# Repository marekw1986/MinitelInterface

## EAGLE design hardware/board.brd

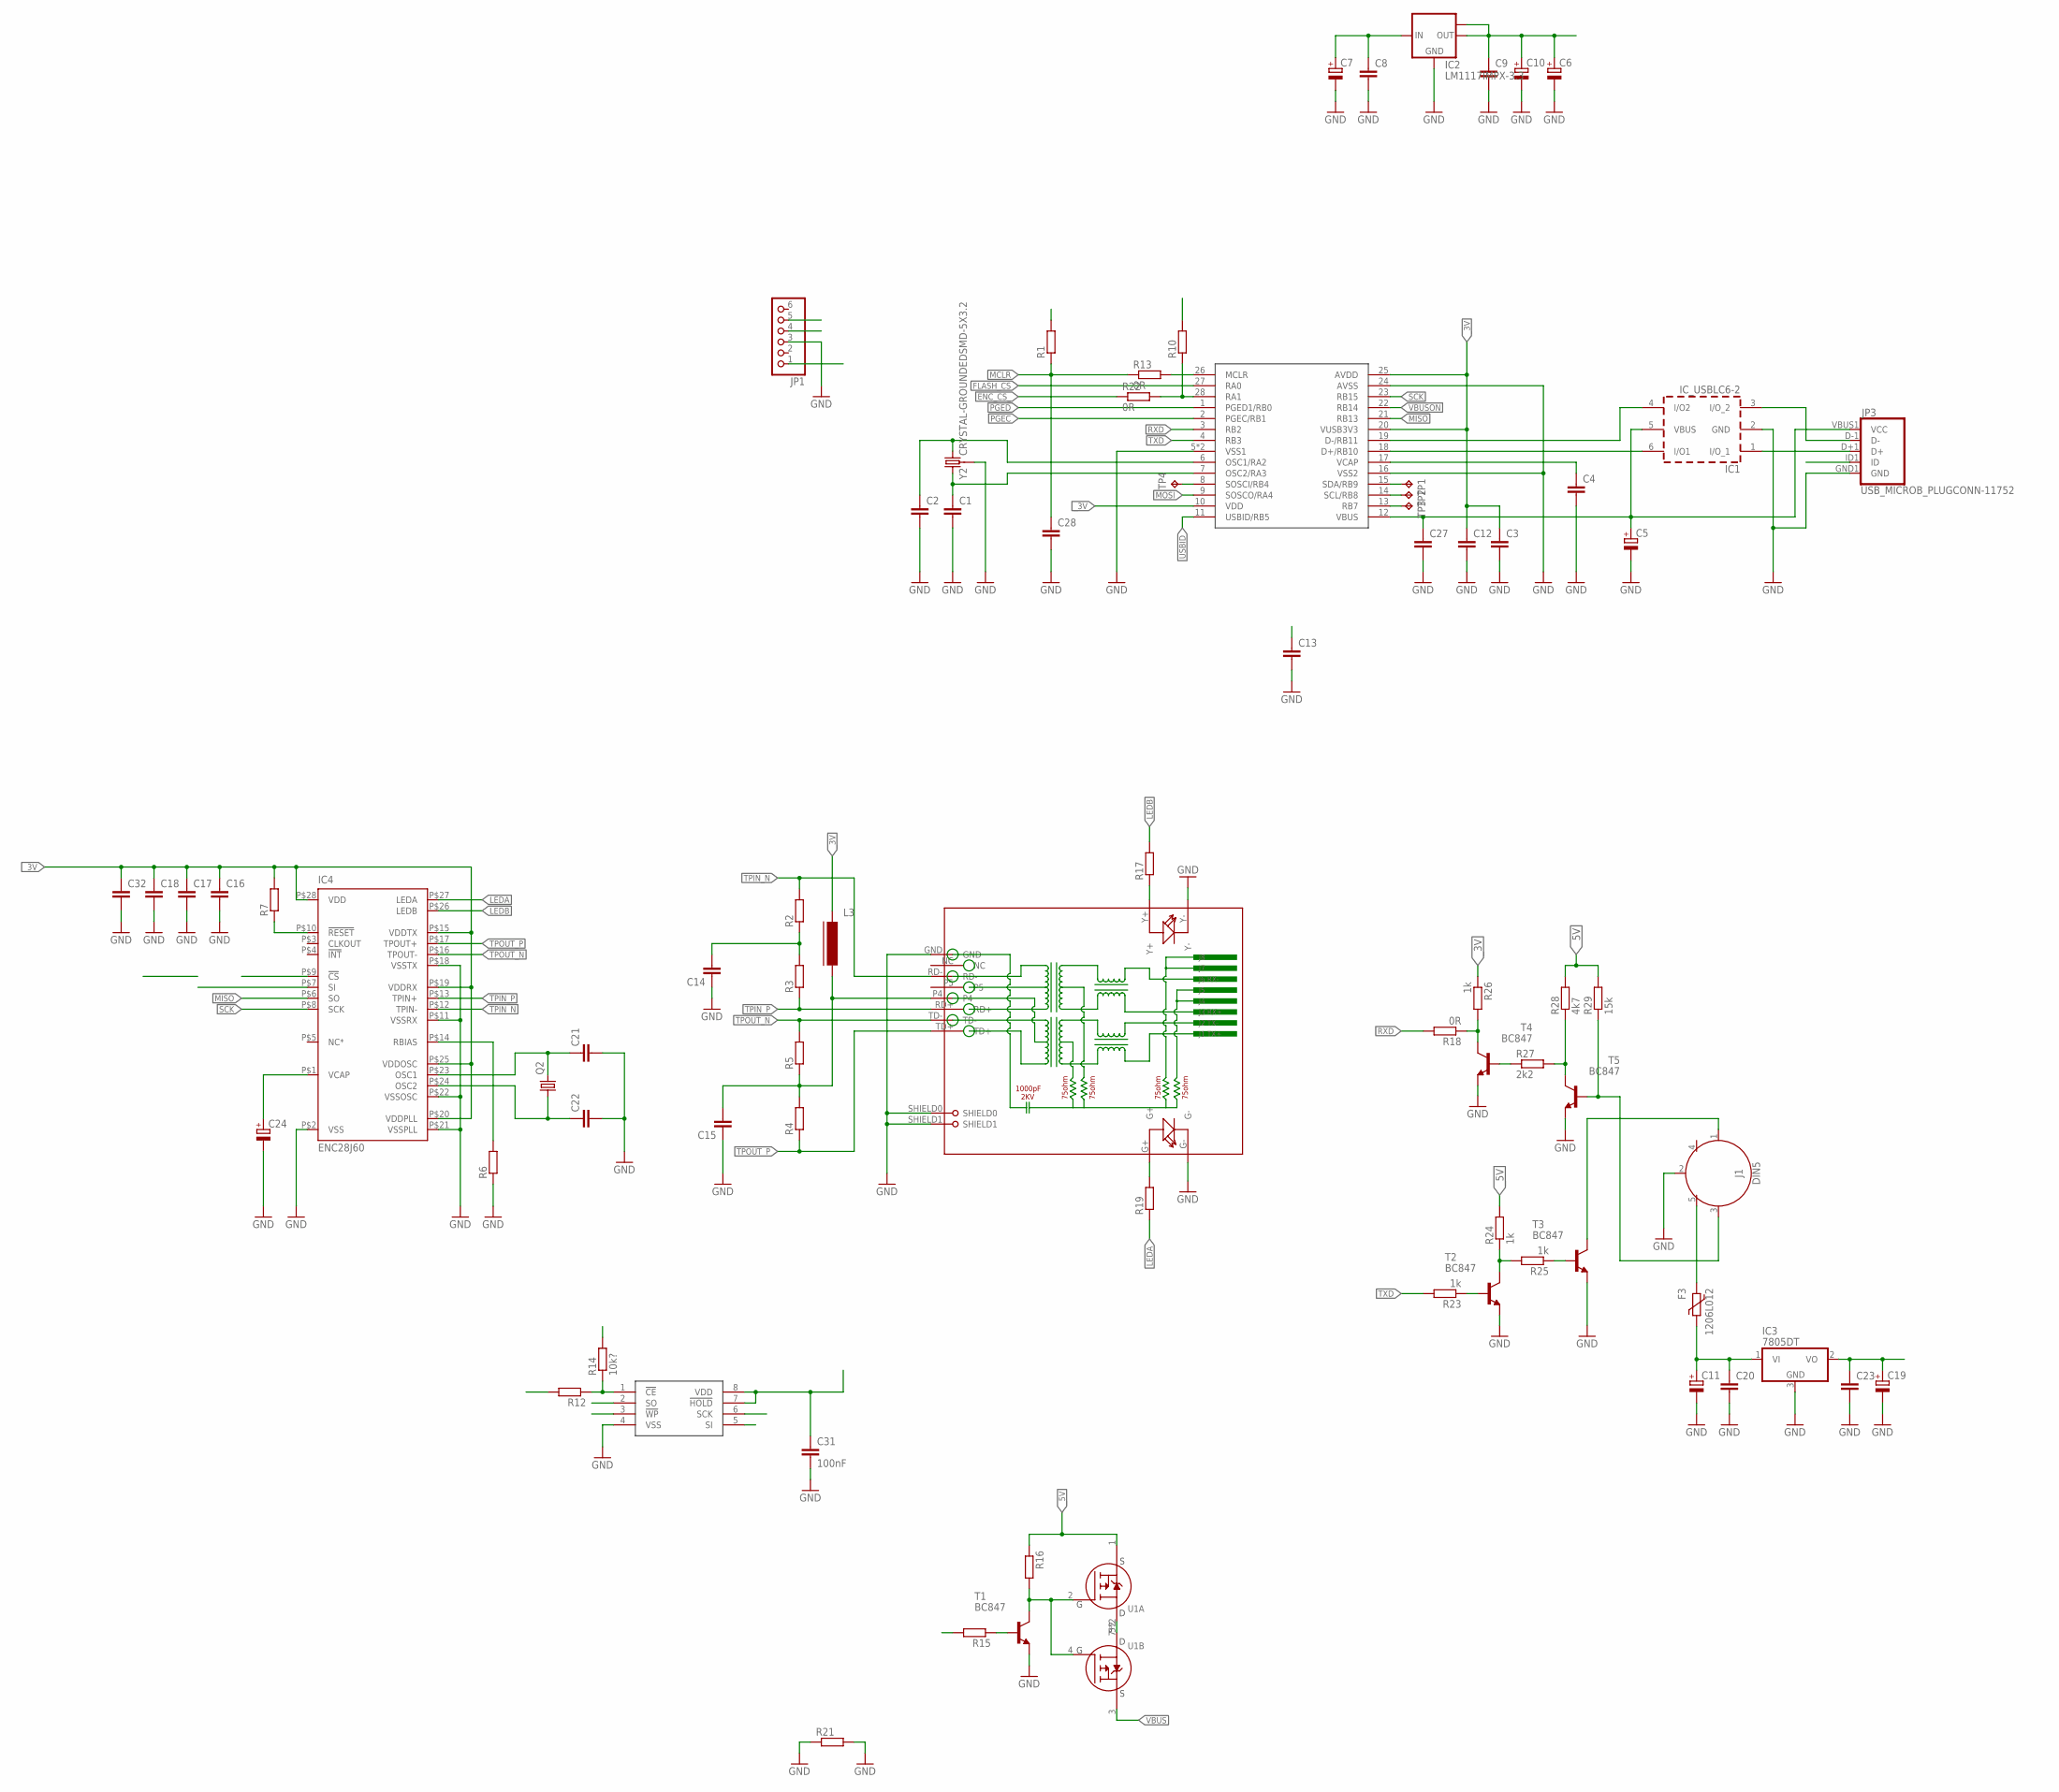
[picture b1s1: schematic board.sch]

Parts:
C1, C2, C4, C8, C9, C12, C13, C14, C15, C20, C21, C22, C23, C27, C28: C-EUC0603; C0603
C3, C16, C17, C18, C32: C-EUC0402; C0402
C5, C6, C24: CPOL-EUSMCA; SMC_A
C7, C11, C19: CPOL-EUSMCC; SMC_C
C10: CPOL-EUSMCB; SMC_B
C31: 100nF; C0603
F3: 1206L012; 1206L
IC1: IC_USBLC6-2; SOT-23-6L
IC2: LM1117IMPX-3.3; SOT223
IC3: 7805DT; TO252
IC4: ENC28J60; TSSOP28W
J1: DIN5; DIN5-RA-PTH
JP1: PINHD-1X6; 1X06
JP3: USB_MICROB_PLUGCONN-11752; USB-B-MICRO-SMD_V03
L3: FERRITE-0805; FB805
Q2: CRYSTALHC49S; HC49/S
R1, R2, R3, R4, R5, R7, R10, R12, R15: R-EU_R0603; R0603
R6: R-EU_R0805; R0805
R13, R22: 0R; R0603
R14: 10k?; R0603
R16: R-EU_R0402; R0402
R17, R19, R21: R-EU_R1206; R1206
R18: 0R; R1206
R23: 1k; R1206
R24, R25, R26: 1k; R0603
R27: 2k2; R0603
R28: 4k7; R0603
R29: 15k; R0603
RJ1: HR911105A
T1, T2, T3, T4, T5: BC847; SOT23
TP1, TP2, TP3, TP4: TPTP16R; TP16R
U1: IRF7314_P_MOSFET; SO-8
U$1: PIC32MX250F128B; QFN-S28-6X6
U$2: SST25VF016BSO8M; SO-08M
Y2: CRYSTAL-GROUNDEDSMD-5X3.2; CRYSTAL-SMD-5X3.2-4PAD

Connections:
D_N: IC1.4 (I/O2), U$1.19 (D-/RB11)
D_P: IC1.6 (I/O1), U$1.18 (D+/RB10)
ENC_CS_: IC4.P$9 (!CS), R22.1
ENC_RST: IC4.P$10 (!RESET), R7.1
FLASH_CS: R12.2, U$1.27 (RA0)
GND: C1.2, C2.2, C3.2, C4.2, C5.-, C6.-, C7.-, C8.2, C9.2, C10.-, C11.-, C12.2, C13.2, C14.1, C15.1, C16.2, C17.2, C18.2, C19.-, C20.2, C21.2, C22.2, C23.2, C24.-, C27.2, C28.2, C31.2, C32.2, IC1.2 (GND), IC2.1 (GND), IC3.3 (GND), IC4.P$2 (VSS), IC4.P$11 (VSSRX), IC4.P$18 (VSSTX), IC4.P$21 (VSSPLL), IC4.P$22 (VSSOSC), J1.2, JP1.3, JP3.GND1 (GND), R6.1, R21.1, R21.2, RJ1.G-, RJ1.GND, RJ1.SHIELD0, RJ1.SHIELD1, RJ1.Y-, T1.2 (E), T2.2 (E), T3.2 (E), T4.2 (E), T5.2 (E), U$1.5 (VSS1), U$1.16 (VSS2), U$1.24 (AVSS), U$1.EXP (VSS1), U$2.4 (VSS), Y2.2 (3), Y2.4 (3)
IO_INT: TP3.TP, U$1.13 (RB7)
LEDA: IC4.P$27 (LEDA), R19.1
LEDB: IC4.P$26 (LEDB), R17.2
MCLR: C28.1, JP1.1, R1.1, R13.1
MCLR_: R13.2, U$1.26 (MCLR)
MISO: IC4.P$6 (SO), U$1.21 (RB13), U$2.2 (SO)
MOSI: IC4.P$7 (SI), U$1.9 (SOSCO/RA4), U$2.5 (SI)
unnamed: R15.1, T1.1 (B)
unnamed: C14.2, R2.1, R3.2
unnamed: J1.1, T3.3 (C)
unnamed: C1.1, U$1.7 (OSC2/RA3), Y2.3 (1)
unnamed: C2.1, U$1.6 (OSC1/RA2), Y2.1 (2)
unnamed: C15.2, L3.2, R4.2, R5.1, RJ1.P4
unnamed: C4.1, U$1.17 (VCAP)
unnamed: F3.2, J1.5
unnamed: IC1.1 (I/O_1), JP3.D+1 (D+)
unnamed: IC1.3 (I/O_2), JP3.D-1 (D-)
unnamed: R12.1, R14.1, U$2.1 (!CE)
unnamed: IC4.P$14 (RBIAS), R6.2
unnamed: R16.2, T1.3 (C), U1.2 (G), U1.4 (G)
unnamed: R10.1, R22.2, U$1.28 (RA1)
unnamed: U1.5 (D), U1.6 (D), U1.7 (D), U1.8 (D)
unnamed: R23.1, T2.1 (B)
unnamed: C21.1, IC4.P$23 (OSC1), Q2.2
unnamed: C22.1, IC4.P$24 (OSC2), Q2.1
unnamed: R24.1, R25.2, T2.3 (C)
unnamed: R25.1, T3.1 (B)
unnamed: R27.1, T4.1 (B)
unnamed: R18.1, R26.2, T4.3 (C)
unnamed: R27.2, R28.1, T5.3 (C)
unnamed: C24.+, IC4.P$1 (VCAP)
unnamed: R17.1, RJ1.Y+
unnamed: R19.2, RJ1.G+
unnamed: J1.3, R29.1, T5.1 (B)
unnamed: C11.+, C20.1, F3.1, IC3.1 (VI)
PGEC: JP1.5, U$1.2 (PGEC/RB1)
PGED: JP1.4, U$1.1 (PGED1/RB0)
RX: TP2.TP, U$1.14 (SCL/RB8)
RXD: R18.2, U$1.3 (RB2)
SCK: IC4.P$8 (SCK), U$1.23 (RB15), U$2.6 (SCK)
SIG: TP4.TP, U$1.8 (SOSCI/RB4)
TPIN_N: IC4.P$12 (TPIN-), R2.2, RJ1.RD-
TPIN_P: IC4.P$13 (TPIN+), R3.1, RJ1.RD+
TPOUT_N: IC4.P$16 (TPOUT-), R5.2, RJ1.TD-
TPOUT_P: IC4.P$17 (TPOUT+), R4.1, RJ1.TD+
TX: TP1.TP, U$1.15 (SDA/RB9)
TXD: R23.2, U$1.4 (RB3)
USBID: JP3.ID1 (ID), U$1.11 (USBID/RB5)
VBUS: C5.+, C27.1, IC1.5 (VBUS), JP3.VBUS1 (VCC), U1.3 (S), U$1.12 (VBUS)
VBUSON: R15.2, U$1.22 (RB14)
_3V: C3.1, C6.+, C9.1, C10.+, C12.1, C13.1, C16.1, C17.1, C18.1, C31.1, C32.1, IC2.2 (OUT), IC2.TAB (OUT1), IC4.P$15 (VDDTX), IC4.P$19 (VDDRX), IC4.P$20 (VDDPLL), IC4.P$25 (VDDOSC), IC4.P$28 (VDD), L3.1, R1.2, R7.2, R10.2, R14.2, R26.1, U$1.10 (VDD), U$1.20 (VUSB3V3), U$1.25 (AVDD), U$2.3 (!WP), U$2.7 (!HOLD), U$2.8 (VDD)
_5V: C7.+, C8.1, C19.+, C23.1, IC2.3 (IN), IC3.2 (VO), R16.1, R24.2, R28.2, R29.2, U1.1 (S)

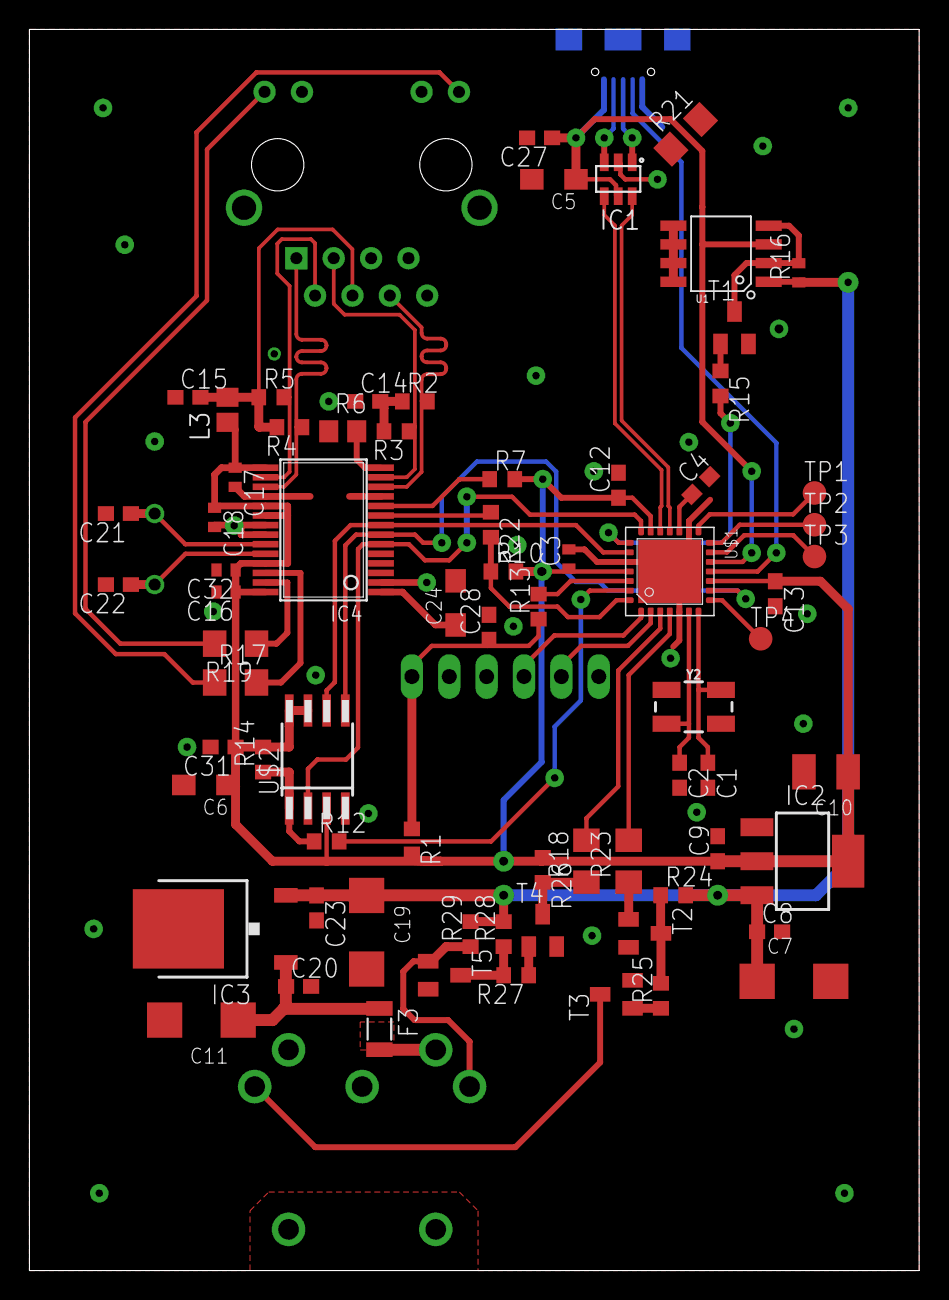
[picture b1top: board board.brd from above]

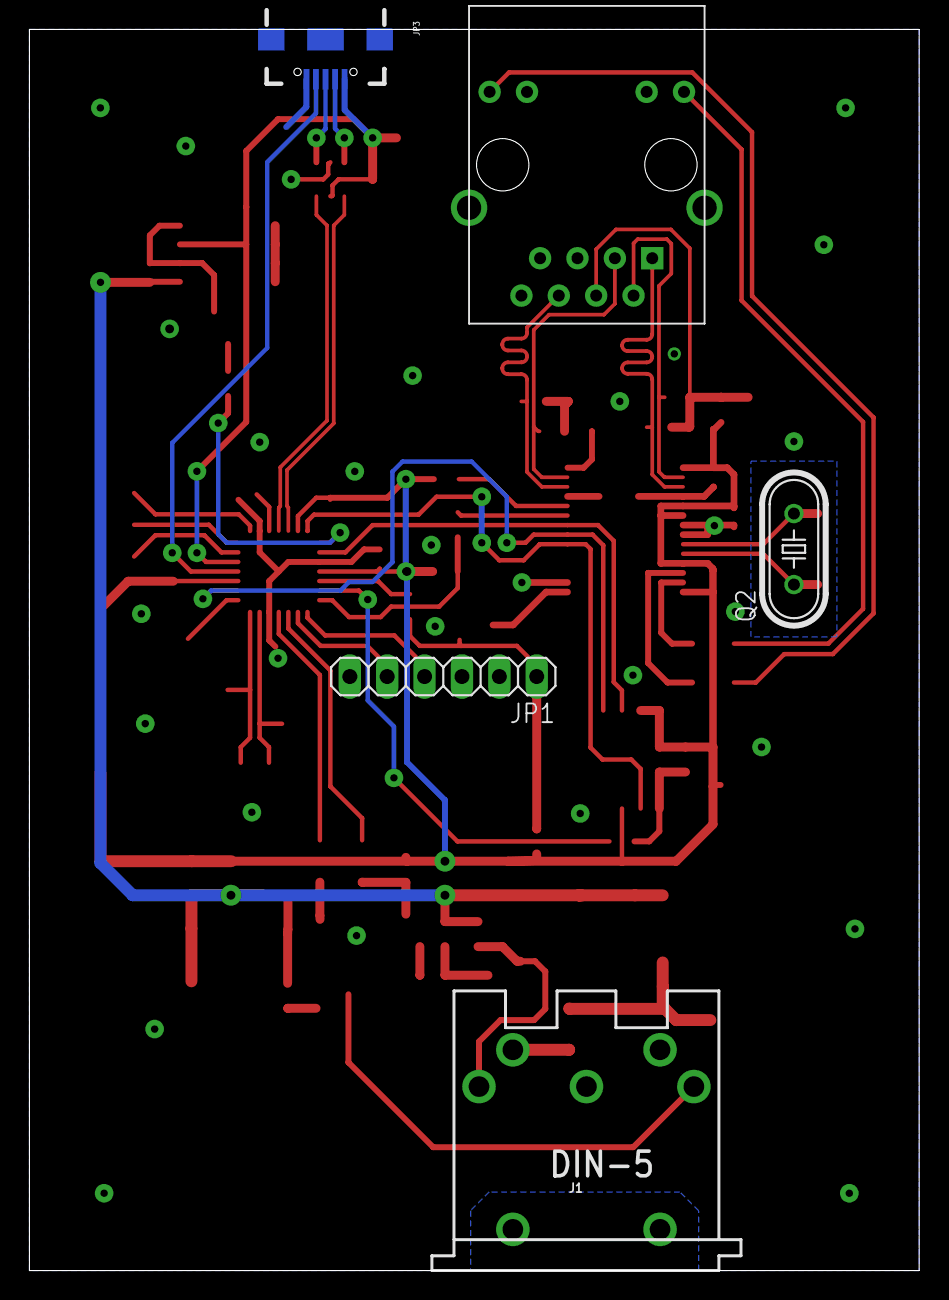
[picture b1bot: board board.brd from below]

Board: 2 copper layers, 60.5 x 84.3 mm, 77 parts (5 on the bottom side), 58 nets.

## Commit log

2024-01-01 Code uploaded
2024-01-02 USB Application code added
2024-01-13 CDC Device works
2024-01-13 Small changes

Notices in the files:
parts and their libraries:
SparkFun-Connectors: Licensing: Creative Commons ShareAlike 4.0 International - https://creativecommons.org/licenses/by-sa/4.0
